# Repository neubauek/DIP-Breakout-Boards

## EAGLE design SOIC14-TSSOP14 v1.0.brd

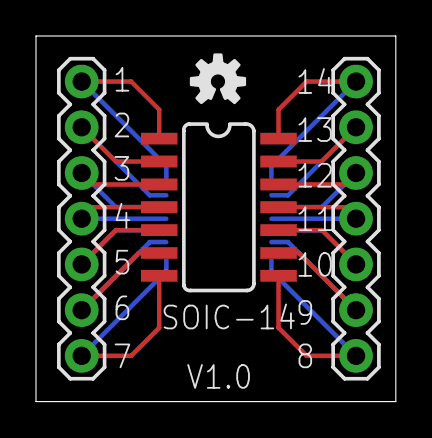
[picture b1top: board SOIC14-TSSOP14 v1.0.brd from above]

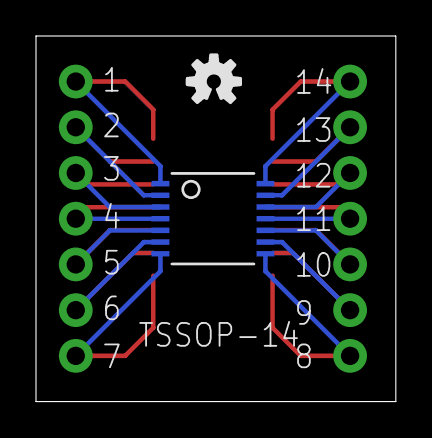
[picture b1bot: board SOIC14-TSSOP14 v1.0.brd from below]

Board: 2 copper layers, 20.0 x 20.3 mm, 7 parts (2 on the bottom side), 14 nets.

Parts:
FRAME1: FRAME-LETTER; CREATIVE_COMMONS
JP1, JP2: 1X07
U$1: SOIC-14
U$2: TSSOP-14; TSSOP14
U$3, U$4: OSHW-LOGO-S

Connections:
unnamed: JP1.7, U$1.1, U$2.14
unnamed: JP1.6, U$1.2, U$2.13
unnamed: JP1.5, U$1.3, U$2.12
unnamed: JP1.4, U$1.4, U$2.11
unnamed: JP1.3, U$1.5, U$2.10
unnamed: JP1.2, U$1.6, U$2.9
unnamed: JP1.1, U$1.7, U$2.8
unnamed: JP2.7, U$1.14, U$2.1
unnamed: JP2.6, U$1.13, U$2.2
unnamed: JP2.5, U$1.12, U$2.3
unnamed: JP2.4, U$1.11, U$2.4
unnamed: JP2.3, U$1.10, U$2.5
unnamed: JP2.2, U$1.9, U$2.6
unnamed: JP2.1, U$1.8, U$2.7

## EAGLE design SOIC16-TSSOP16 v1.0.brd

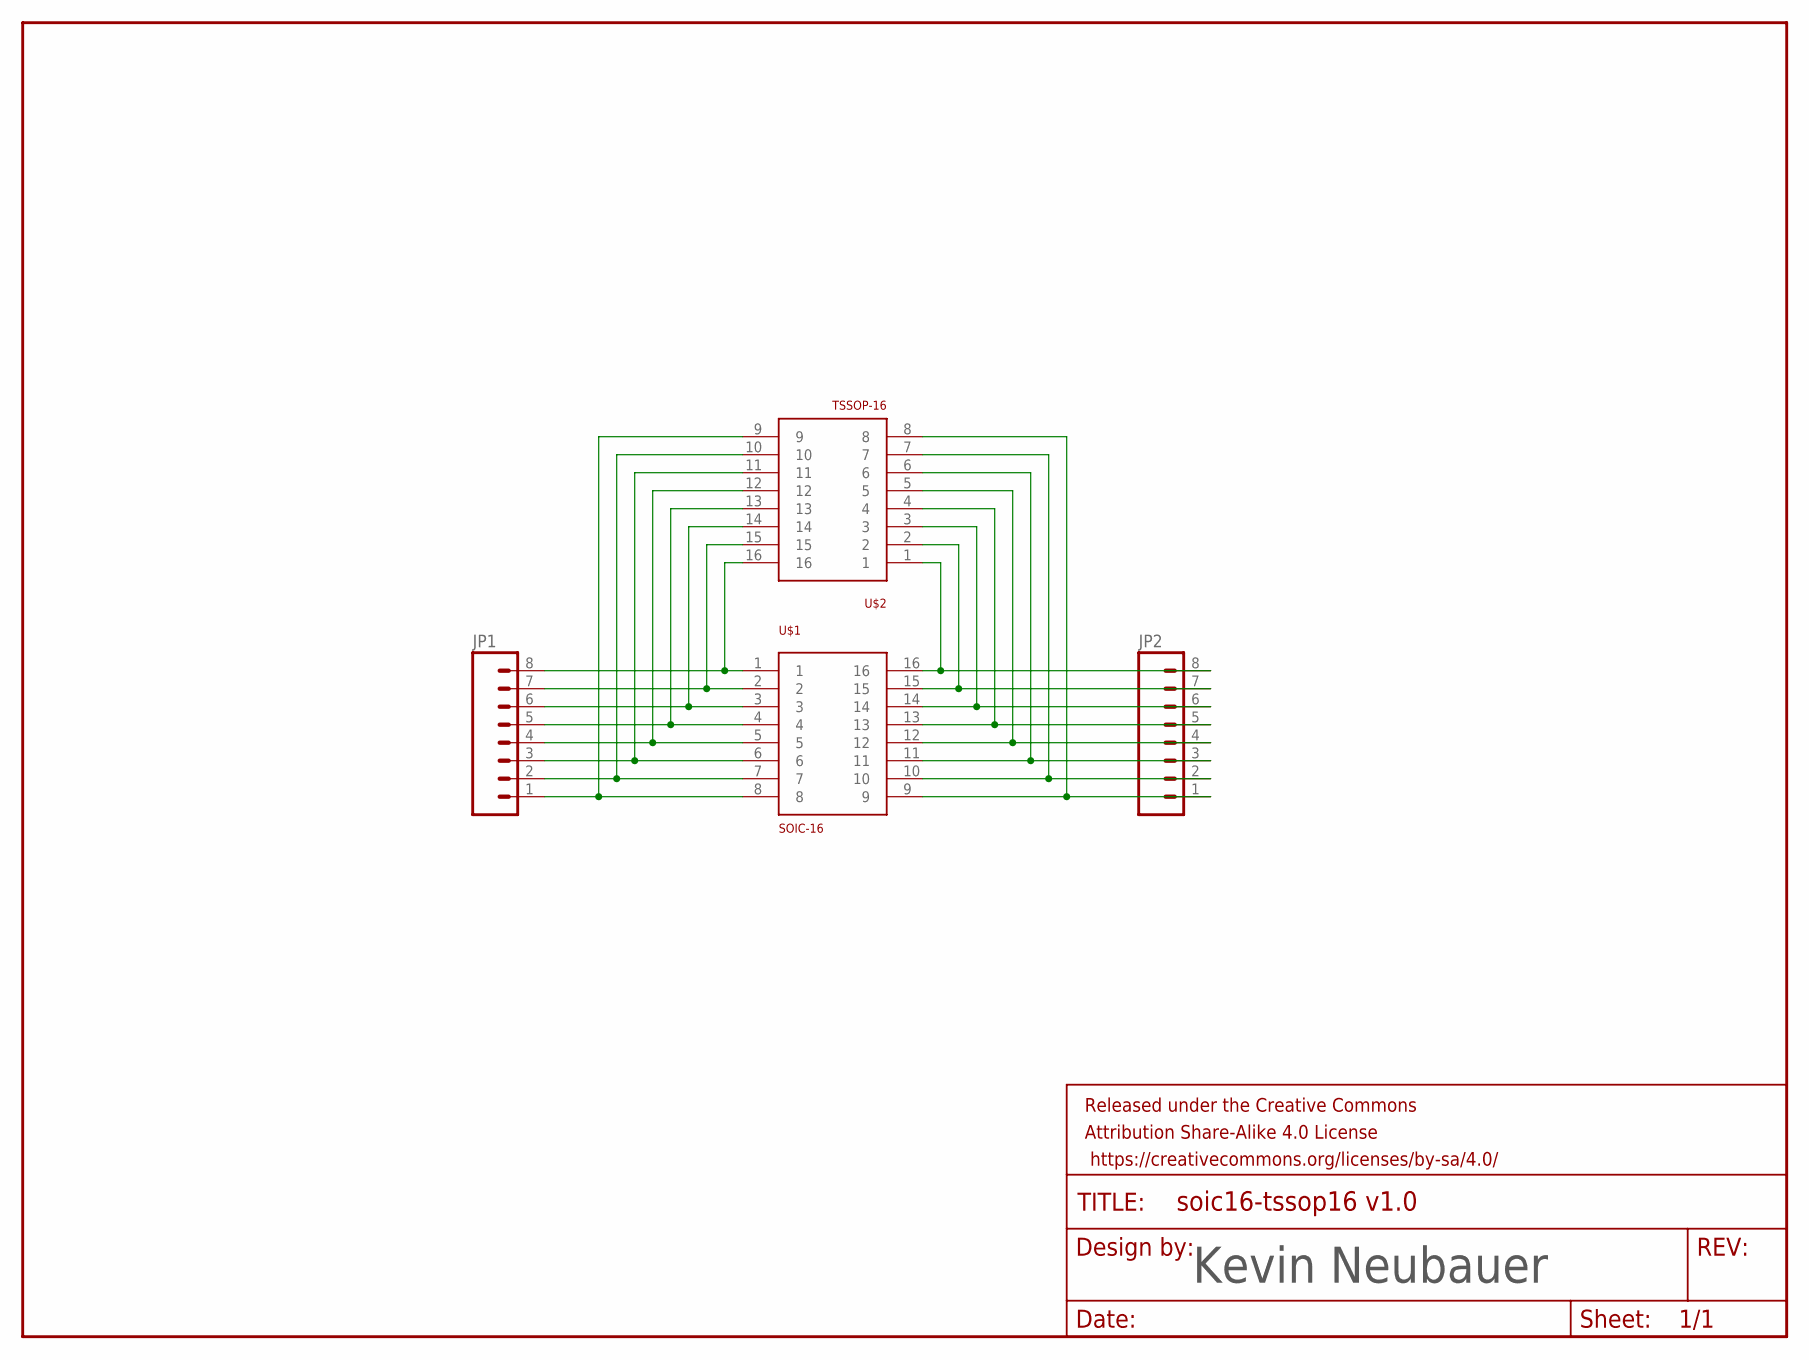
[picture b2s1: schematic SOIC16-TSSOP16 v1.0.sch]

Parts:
FRAME1: FRAME-LETTER; CREATIVE_COMMONS
JP1, JP2: M08NO_SILK; 1X08_NO_SILK
U$1: SOIC-16; SO16
U$2: TSSOP-16; TSSOP16

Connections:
unnamed: JP1.8, U$1.1, U$2.16
unnamed: JP1.7, U$1.2, U$2.15
unnamed: JP1.6, U$1.3, U$2.14
unnamed: JP1.5, U$1.4, U$2.13
unnamed: JP1.4, U$1.5, U$2.12
unnamed: JP1.3, U$1.6, U$2.11
unnamed: JP1.2, U$1.7, U$2.10
unnamed: JP1.1, U$1.8, U$2.9
unnamed: JP2.8, U$1.16, U$2.1
unnamed: JP2.7, U$1.15, U$2.2
unnamed: JP2.6, U$1.14, U$2.3
unnamed: JP2.5, U$1.13, U$2.4
unnamed: JP2.4, U$1.12, U$2.5
unnamed: JP2.3, U$1.11, U$2.6
unnamed: JP2.2, U$1.10, U$2.7
unnamed: JP2.1, U$1.9, U$2.8

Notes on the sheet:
Kevin Neubauer

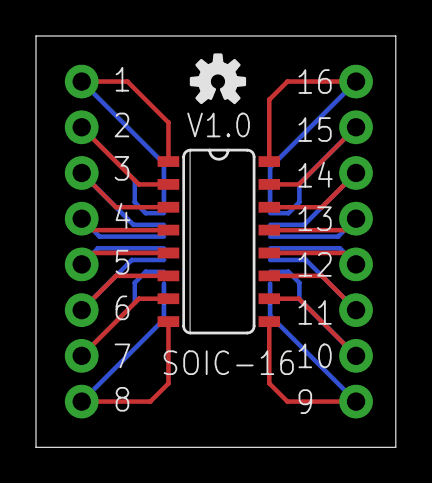
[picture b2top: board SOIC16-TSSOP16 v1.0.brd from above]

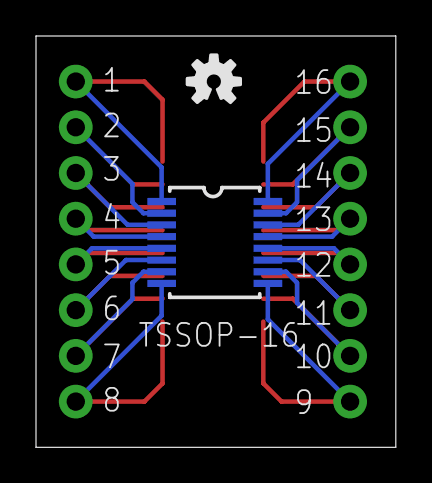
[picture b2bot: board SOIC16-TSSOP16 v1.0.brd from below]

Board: 2 copper layers, 20.0 x 22.9 mm, 7 parts (2 on the bottom side), 16 nets.

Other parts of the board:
U$3, U$4: OSHW-LOGO-S

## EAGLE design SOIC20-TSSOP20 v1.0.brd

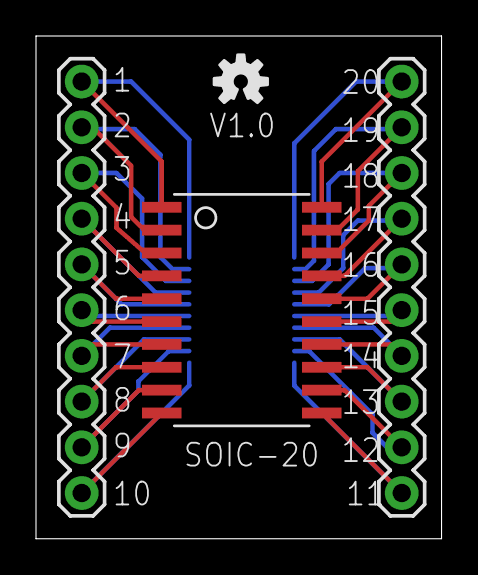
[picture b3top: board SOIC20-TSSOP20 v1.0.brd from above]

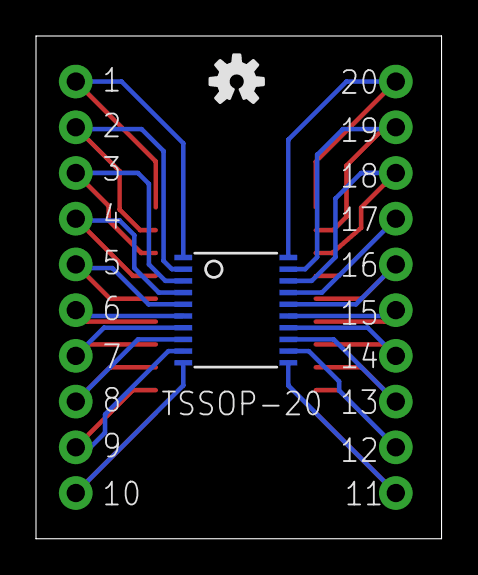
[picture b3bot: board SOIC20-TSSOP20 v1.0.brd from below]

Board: 2 copper layers, 22.5 x 27.9 mm, 7 parts (2 on the bottom side), 20 nets.

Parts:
FRAME1: FRAME-LETTER; CREATIVE_COMMONS
JP1, JP2: M10"; 1X10
U$1: SOIC-20
U$2: TSSOP-20; TSSOP20
U$3, U$4: OSHW-LOGO-S

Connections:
unnamed: JP1.10, U$1.1, U$2.20
unnamed: JP1.9, U$1.2, U$2.19
unnamed: JP1.8, U$1.3, U$2.18
unnamed: JP1.7, U$1.4, U$2.17
unnamed: JP1.6, U$1.5, U$2.16
unnamed: JP1.5, U$1.6, U$2.15
unnamed: JP1.4, U$1.7, U$2.14
unnamed: JP1.3, U$1.8, U$2.13
unnamed: JP1.2, U$1.9, U$2.12
unnamed: JP1.1, U$1.10, U$2.11
unnamed: JP2.10, U$1.20, U$2.1
unnamed: JP2.9, U$1.19, U$2.2
unnamed: JP2.8, U$1.18, U$2.3
unnamed: JP2.7, U$1.17, U$2.4
unnamed: JP2.6, U$1.16, U$2.5
unnamed: JP2.5, U$1.15, U$2.6
unnamed: JP2.4, U$1.14, U$2.7
unnamed: JP2.3, U$1.13, U$2.8
unnamed: JP2.2, U$1.12, U$2.9
unnamed: JP2.1, U$1.11, U$2.10

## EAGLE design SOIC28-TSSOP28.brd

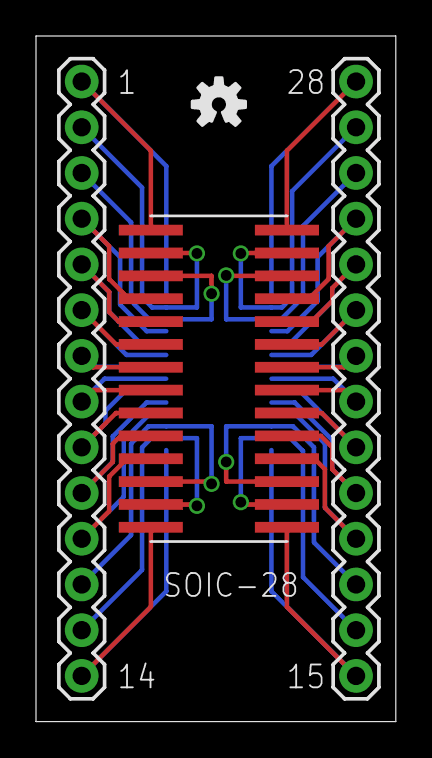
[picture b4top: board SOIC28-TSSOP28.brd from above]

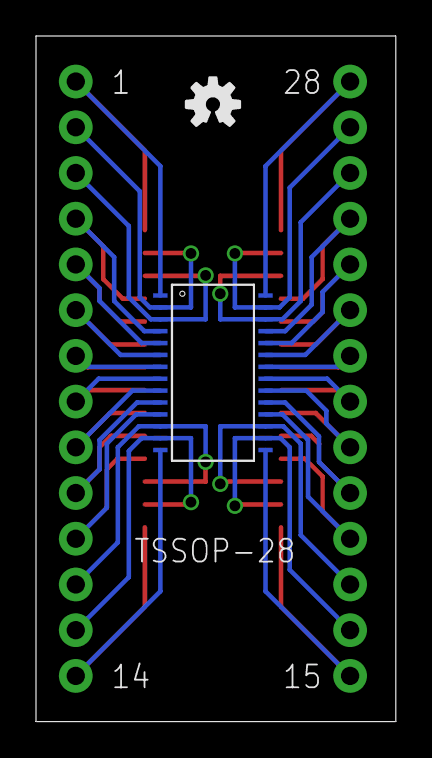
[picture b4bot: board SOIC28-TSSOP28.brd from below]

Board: 2 copper layers, 20.0 x 38.1 mm, 7 parts (2 on the bottom side), 28 nets.

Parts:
FRAME1: FRAME-LETTER; CREATIVE_COMMONS
JP1, JP2: M14; 1X14
U$1: SOIC-28
U$2: TSSOP-28; TSSOP28
U$3, U$4: OSHW-LOGO-S

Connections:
unnamed: JP1.14, U$1.P1, U$2.28
unnamed: JP1.13, U$1.P2, U$2.27
unnamed: JP2.14, U$1.P28, U$2.1
unnamed: JP2.13, U$1.P27, U$2.2
unnamed: JP2.12, U$1.P26, U$2.3
unnamed: JP2.11, U$1.P25, U$2.4
unnamed: JP2.10, U$1.P24, U$2.5
unnamed: JP2.9, U$1.P23, U$2.6
unnamed: JP2.8, U$1.P22, U$2.7
unnamed: JP2.7, U$1.P21, U$2.8
unnamed: JP2.6, U$1.P20, U$2.9
unnamed: JP2.5, U$1.P19, U$2.10
unnamed: JP1.2, U$1.P13, U$2.16
unnamed: JP1.1, U$1.P14, U$2.15
unnamed: JP2.4, U$1.P18, U$2.11
unnamed: JP2.3, U$1.P17, U$2.12
unnamed: JP2.2, U$1.P16, U$2.13
unnamed: JP2.1, U$1.P15, U$2.14
unnamed: JP1.3, U$1.P12, U$2.17
unnamed: JP1.4, U$1.P11, U$2.18
unnamed: JP1.5, U$1.P10, U$2.19
unnamed: JP1.6, U$1.P9, U$2.20
unnamed: JP1.8, U$1.P7, U$2.22
unnamed: JP1.7, U$1.P8, U$2.21
unnamed: JP1.10, U$1.P5, U$2.24
unnamed: JP1.9, U$1.P6, U$2.23
unnamed: JP1.12, U$1.P3, U$2.26
unnamed: JP1.11, U$1.P4, U$2.25

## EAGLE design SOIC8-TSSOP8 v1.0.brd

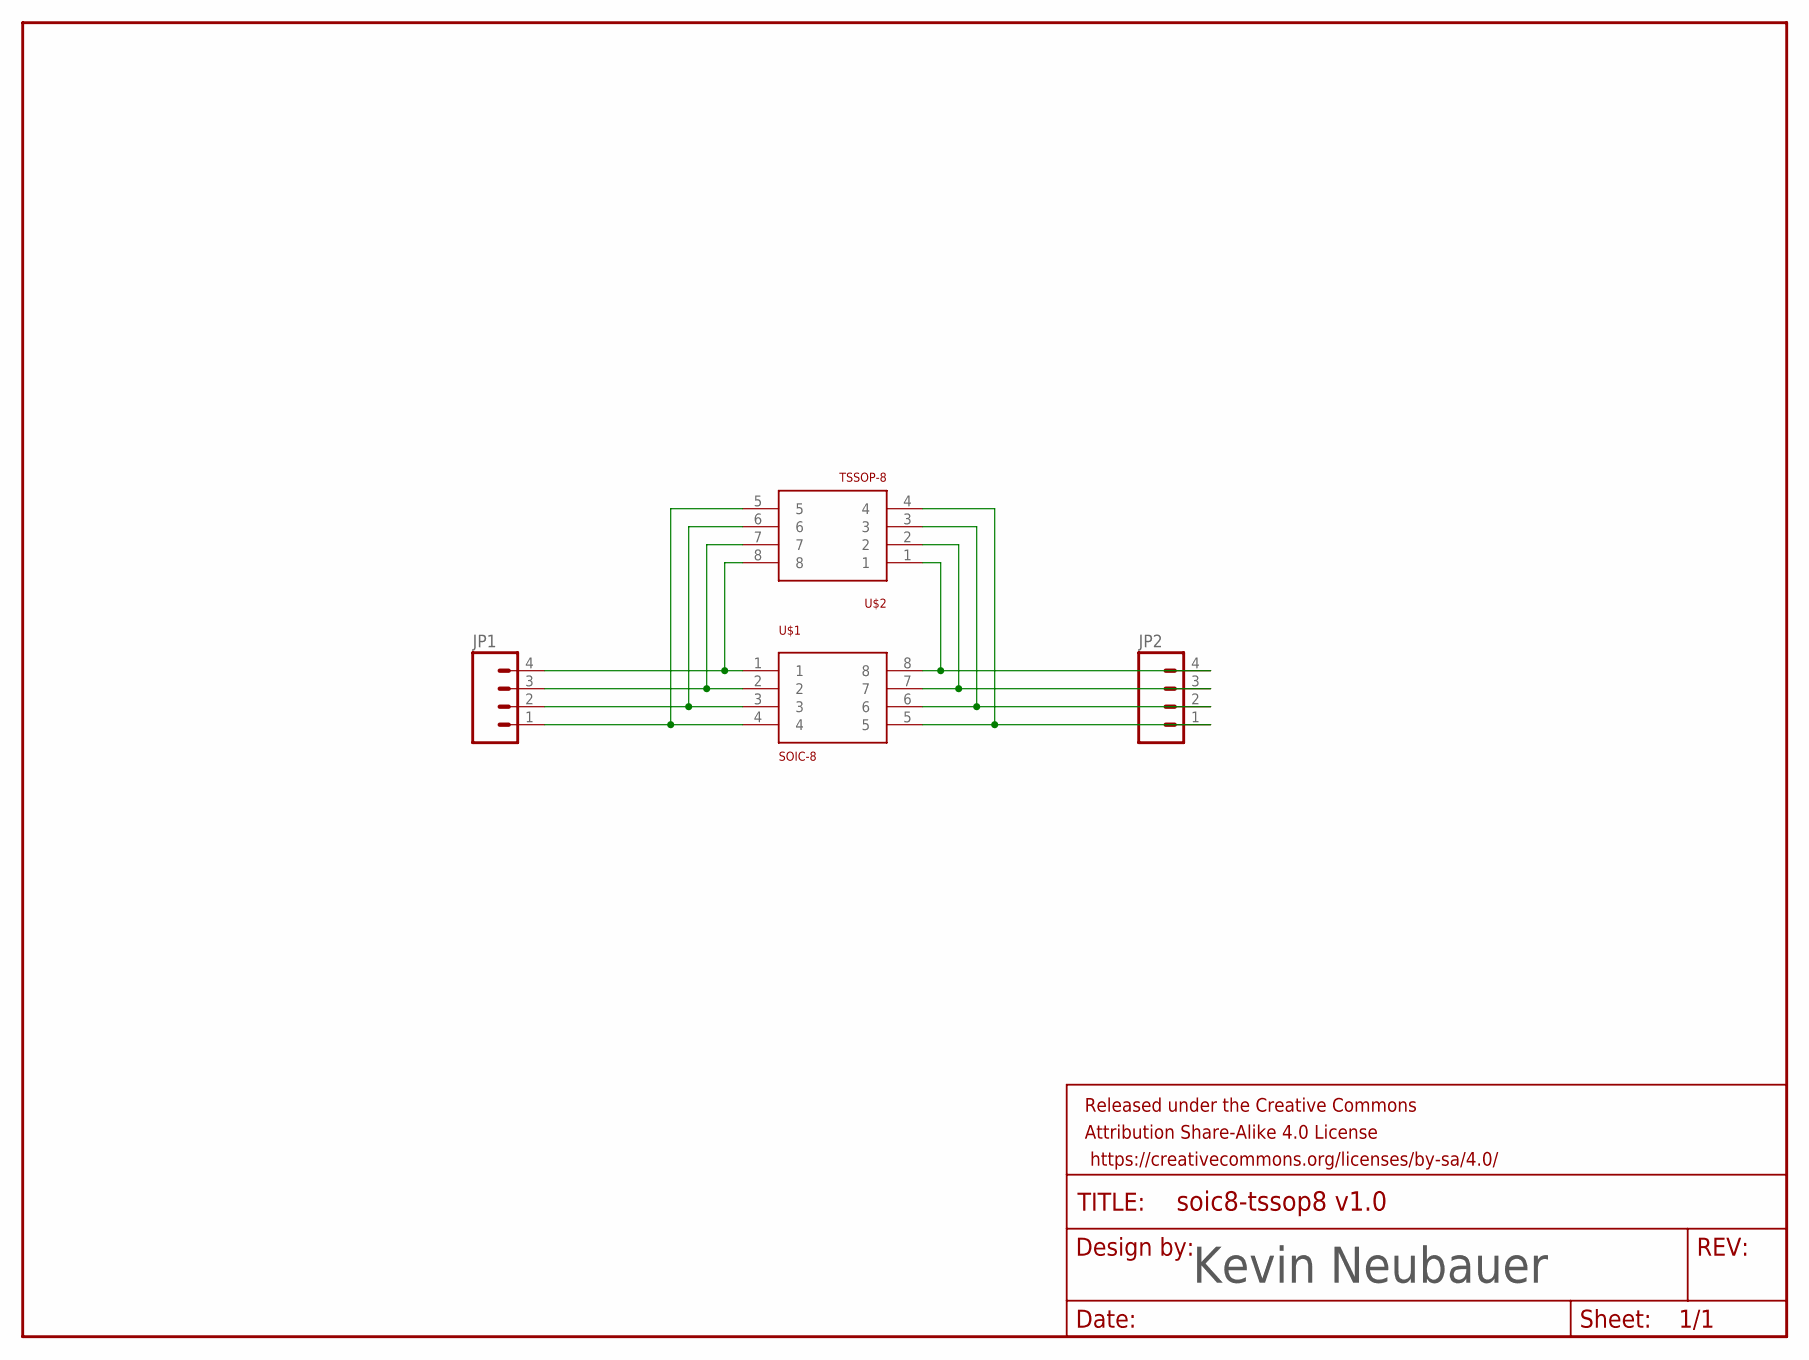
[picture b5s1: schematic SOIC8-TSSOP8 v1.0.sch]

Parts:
FRAME1: FRAME-LETTER; CREATIVE_COMMONS
JP1, JP2: M04PTH; 1X04
U$1: SOIC-8
U$2: TSSOP-8; TSSOP8

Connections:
unnamed: JP1.4, U$1.1, U$2.8
unnamed: JP1.3, U$1.2, U$2.7
unnamed: JP1.2, U$1.3, U$2.6
unnamed: JP1.1, U$1.4, U$2.5
unnamed: JP2.4, U$1.8, U$2.1
unnamed: JP2.3, U$1.7, U$2.2
unnamed: JP2.2, U$1.6, U$2.3
unnamed: JP2.1, U$1.5, U$2.4

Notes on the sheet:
Kevin Neubauer

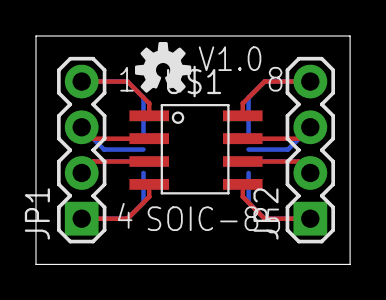
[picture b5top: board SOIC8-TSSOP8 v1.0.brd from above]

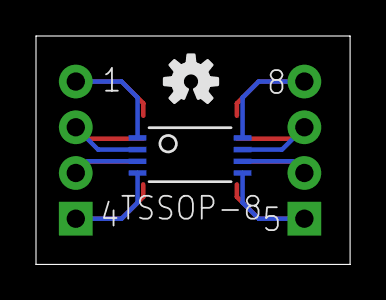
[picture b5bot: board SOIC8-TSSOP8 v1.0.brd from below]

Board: 2 copper layers, 17.4 x 12.7 mm, 7 parts (2 on the bottom side), 8 nets.

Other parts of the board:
U$3, U$4: OSHW-LOGO-S

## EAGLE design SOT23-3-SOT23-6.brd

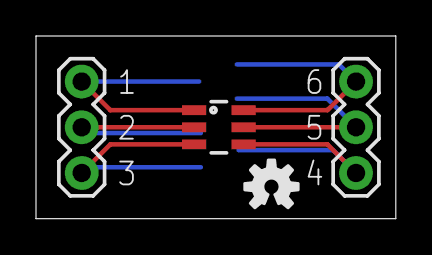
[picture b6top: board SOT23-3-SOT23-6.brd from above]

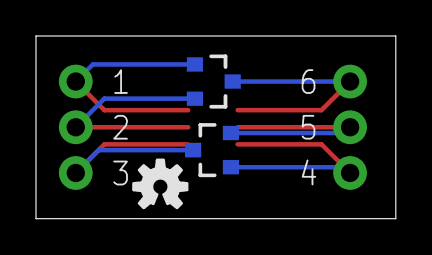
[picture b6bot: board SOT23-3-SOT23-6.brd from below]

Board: 2 copper layers, 20.0 x 10.2 mm, 8 parts (3 on the bottom side), 6 nets.

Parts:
FRAME1: FRAME-LETTER; CREATIVE_COMMONS
JP1, JP2: 1X03
U$1, U$2: OSHW-LOGO-S
U$3, U$4: SOT23-3
U$5: SOT23-6

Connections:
unnamed: JP1.2, U$3.2, U$5.2
unnamed: JP1.1, U$3.1, U$5.3
unnamed: JP2.3, U$4.1, U$5.6
unnamed: JP2.2, U$4.2, U$5.5
unnamed: JP2.1, U$3.3, U$5.4
unnamed: JP1.3, U$4.3, U$5.1

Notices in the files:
parts and their libraries:
SparkFun-Aesthetics: Licensing: Creative Commons ShareAlike 4.0 International - https://creativecommons.org/licenses/by-sa/4.0
SparkFun-Aesthetics: Released under the Creative Commons Attribution Share-Alike 4.0 License
SparkFun-Aesthetics: https://creativecommons.org/licenses/by-sa/4.0
